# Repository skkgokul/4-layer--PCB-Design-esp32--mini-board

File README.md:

# 4 layer  PCB Design esp32  mini board
 ESP 32 mini is a type of  microcontroller  which is uesd to control the IOT devices and  for various projectes

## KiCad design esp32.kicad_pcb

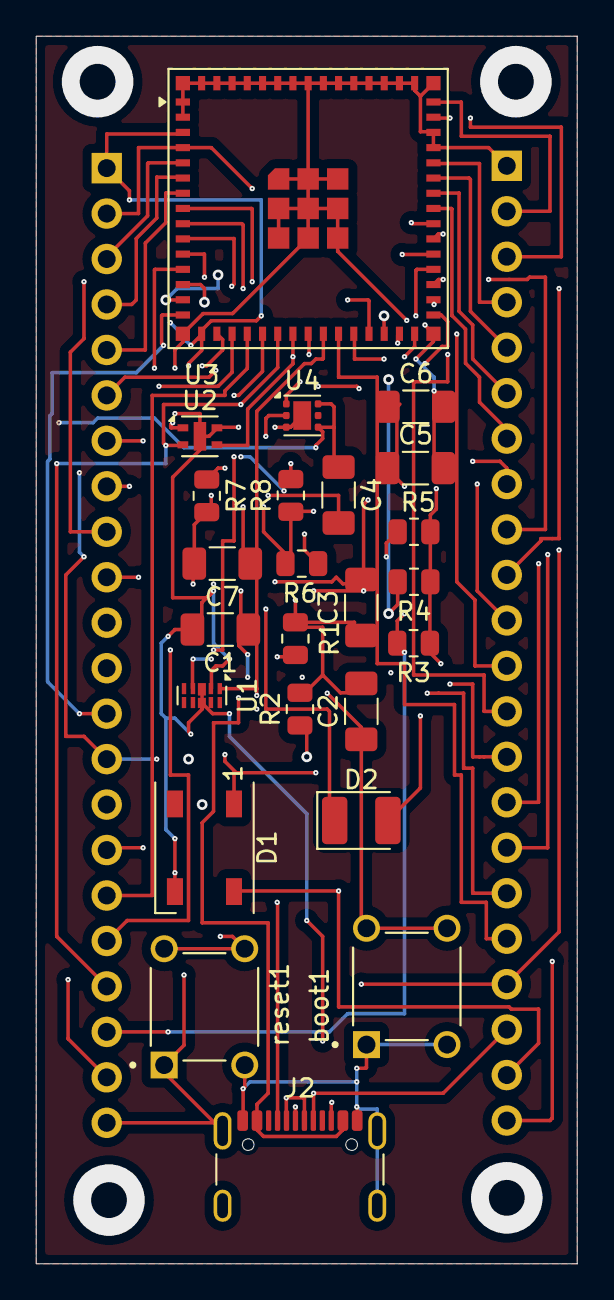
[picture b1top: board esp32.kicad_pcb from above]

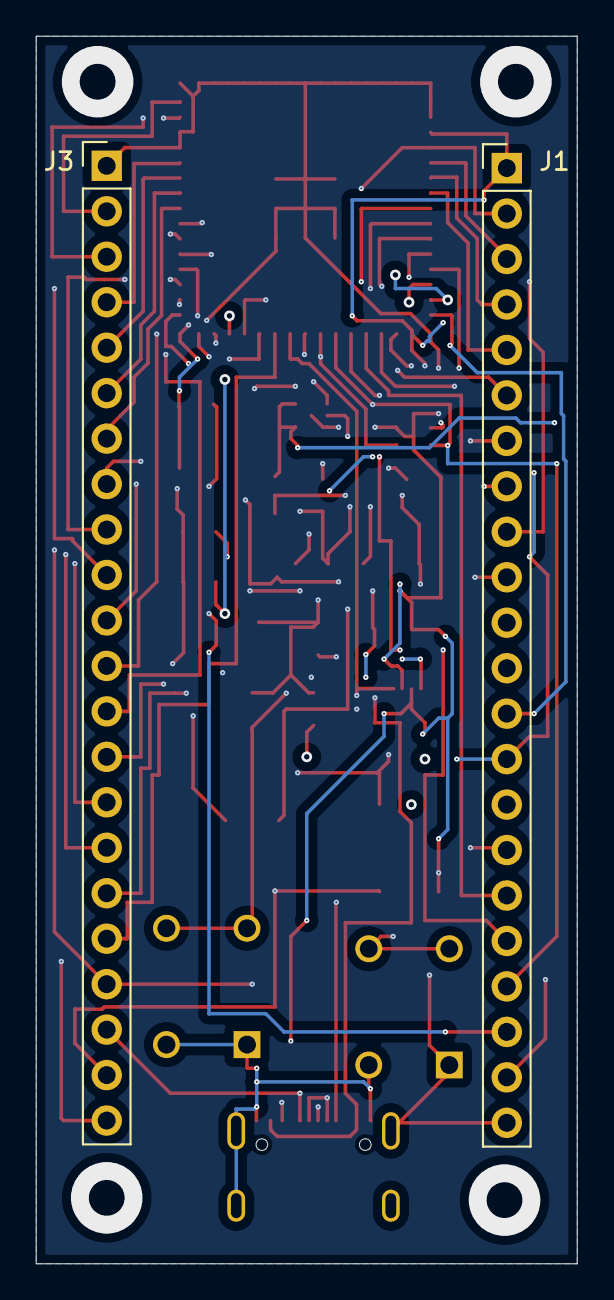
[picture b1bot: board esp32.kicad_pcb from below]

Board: 4 copper layers, 30.2 x 68.6 mm, 26 parts (2 on the bottom side), 41 nets.

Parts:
C1, C2, C3, C5, C6: 0.1uF; C_1206_3216Metric_Pad1.33x1.80mm_HandSolder
C4, C7: 10uF; C_1206_3216Metric_Pad1.33x1.80mm_HandSolder
D1: WS2812B; LED_WS2812B_PLCC4_5.0x5.0mm_P3.2mm
D2: LED; LED_1210_3225Metric_Pad1.42x2.65mm_HandSolder
J1, J3: Conn_01x22_Pin; PinHeader_1x22_P2.54mm_Vertical
J2: USB_C_Receptacle_USB2.0_16P; USB_C_Receptacle_GCT_USB4105-xx-A_16P_TopMnt_Horizontal
R1, R8: 5.1k; R_0805_2012Metric
R2: 5.1K; R_0805_2012Metric
R3, R4, R5: 10K; R_0805_2012Metric
R6: 1M; R_0805_2012Metric
R7: 200k; R_0805_2012Metric
U1: D3V3XA4B10LP; Diodes_UDFN-10_1.0x2.5mm_P0.5mm
U2: ENS210; AMS_QFN-4-1EP_2x2mm_P0.95mm_EP0.7x1.6mm
U3: ESP32-S3-MINI-1; ESP32-S2-MINI-1U
U4: TLV75801PDRV; WSON-6-1EP_2x2mm_P0.65mm_EP1x1.6mm
boot1: TS02-66-95-BK-260-LCR-D; SW_TS02-66-95-BK-260-LCR-D
reset1: TS02-66-95-BK-260-LCR-D; SW_TS02-66-95-BK-260-LCR-D

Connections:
/5VUSB: C4.1, J1.21, U4.4 (EN), U4.6 (IN)
/GPIO0: C2.1, J1.2, U3.4 (IO0), boot1.2, boot1.4
/GPIO1: J1.3, U3.5 (IO1)
/GPIO2: J1.4, U3.6 (IO2)
/GPIO3: J1.5, U3.7 (IO3)
/GPIO4: J1.6, U3.8 (IO4)
/GPIO6: J1.8, U3.10 (IO6)
/GPIO7: J1.9, U3.11 (IO7)
/GPIO8: J1.10, U3.12 (IO8)
/GPIO9: J1.11, U3.13 (IO9)
/GPIO10: J1.12, U3.14 (IO10)
/GPIO11: J1.13, U3.15 (IO11)
/GPIO12: C1.1, C1.2, C2.2, C3.1, C3.2, C5.1, C5.2, C6.1, C6.2, C7.1, D1.1 (VDD), D1.3 (VSS), J1.1, J1.7, J1.14, J1.22, J2.A1 (GND), J2.A6 (D+), J2.A7 (D-), J2.A12 (GND), J2.B1 (GND), J2.B6 (D+), J2.B7 (D-), J2.B12 (GND), J2.S1 (SHIELD), J3.1, J3.2, J3.12, J3.18, J3.19, J3.20, R1.2, R2.2, R3.1, R4.1, R4.2, R5.1, R6.1, R8.1, U1.1, U1.2, U1.3 (VSS), U1.8 (VSS), U1.9 (NC), U2.1 (VDD), U2.4 (GND), U2.5 (GND), U3.1 (GND), U3.2 (GND), U3.3 (3V3), U3.9 (IO5), U3.16 (IO12), U3.23 (IO19), U3.24 (IO20), U3.25 (IO21), U3.33 (IO37), U3.42 (GND), U3.43 (GND), U3.45 (EN), U3.46 (GND), U3.47 (GND), U3.48 (GND), U3.49 (GND), U3.50 (GND), U3.51 (GND), U3.52 (GND), U3.53 (GND), U3.54 (GND), U3.55 (GND), U3.56 (GND), U3.57 (GND), U3.58 (GND), U3.59 (GND), U3.60 (GND), U3.61 (GND), U3.62 (GND), U3.63 (GND), U3.64 (GND), U3.65 (GND), U4.1 (OUT), U4.3 (GND), U4.7 (GND), boot1.1, boot1.3, reset1.1, reset1.2, reset1.3, reset1.4
/GPIO13: J1.15, U3.17 (IO13)
/GPIO14: J1.16, U3.18 (IO14)
/GPIO15: J1.17, U3.19 (IO15)
/GPIO16: J1.18, U3.20 (IO16)
/GPIO26: J3.17, U3.26 (IO26)
/GPIO33: J3.16, U3.28 (IO33)
/GPIO34: J3.15, U3.29 (IO34)
/GPIO35: J3.14, U3.31 (IO35)
/GPIO36: J3.13, U3.32 (IO36)
/GPIO38: J3.11, U3.34 (IO38)
/GPIO39: J3.10, U3.35 (IO39)
/GPIO40: J3.9, U3.36 (IO40)
/GPIO41: J3.8, U3.37 (IO41)
/GPIO42: J3.7, U3.38 (IO42)
/GPIO45: J3.4, U3.41 (IO45)
/GPIO46: J3.3, U3.44 (IO46)
/GPIO47: J3.22, U3.30 (IO48)
/GPIO48: D1.4 (DIN), J3.21, U3.27 (IO47)
/I2C_SCL: J1.19, R5.2, U2.2 (SCL), U3.21 (IO17)
/I2C_SDA: J1.20, R3.2, U2.3 (SDA), U3.22 (IO18)
/RXD: J3.5, U3.40 (RXD0)
/TXD: J3.6, U3.39 (TXD0)
unnamed: D2.2 (A), R8.2
unnamed: C4.2, C7.2, D2.1 (K), R7.2
unnamed: J2.A5 (CC1), R1.1
unnamed: J2.B5 (CC2), R2.1
unnamed: J2.A4 (VBUS), J2.A9 (VBUS), J2.B4 (VBUS), J2.B9 (VBUS), U1.4
unnamed: R6.2, R7.1, U4.2 (FB)
